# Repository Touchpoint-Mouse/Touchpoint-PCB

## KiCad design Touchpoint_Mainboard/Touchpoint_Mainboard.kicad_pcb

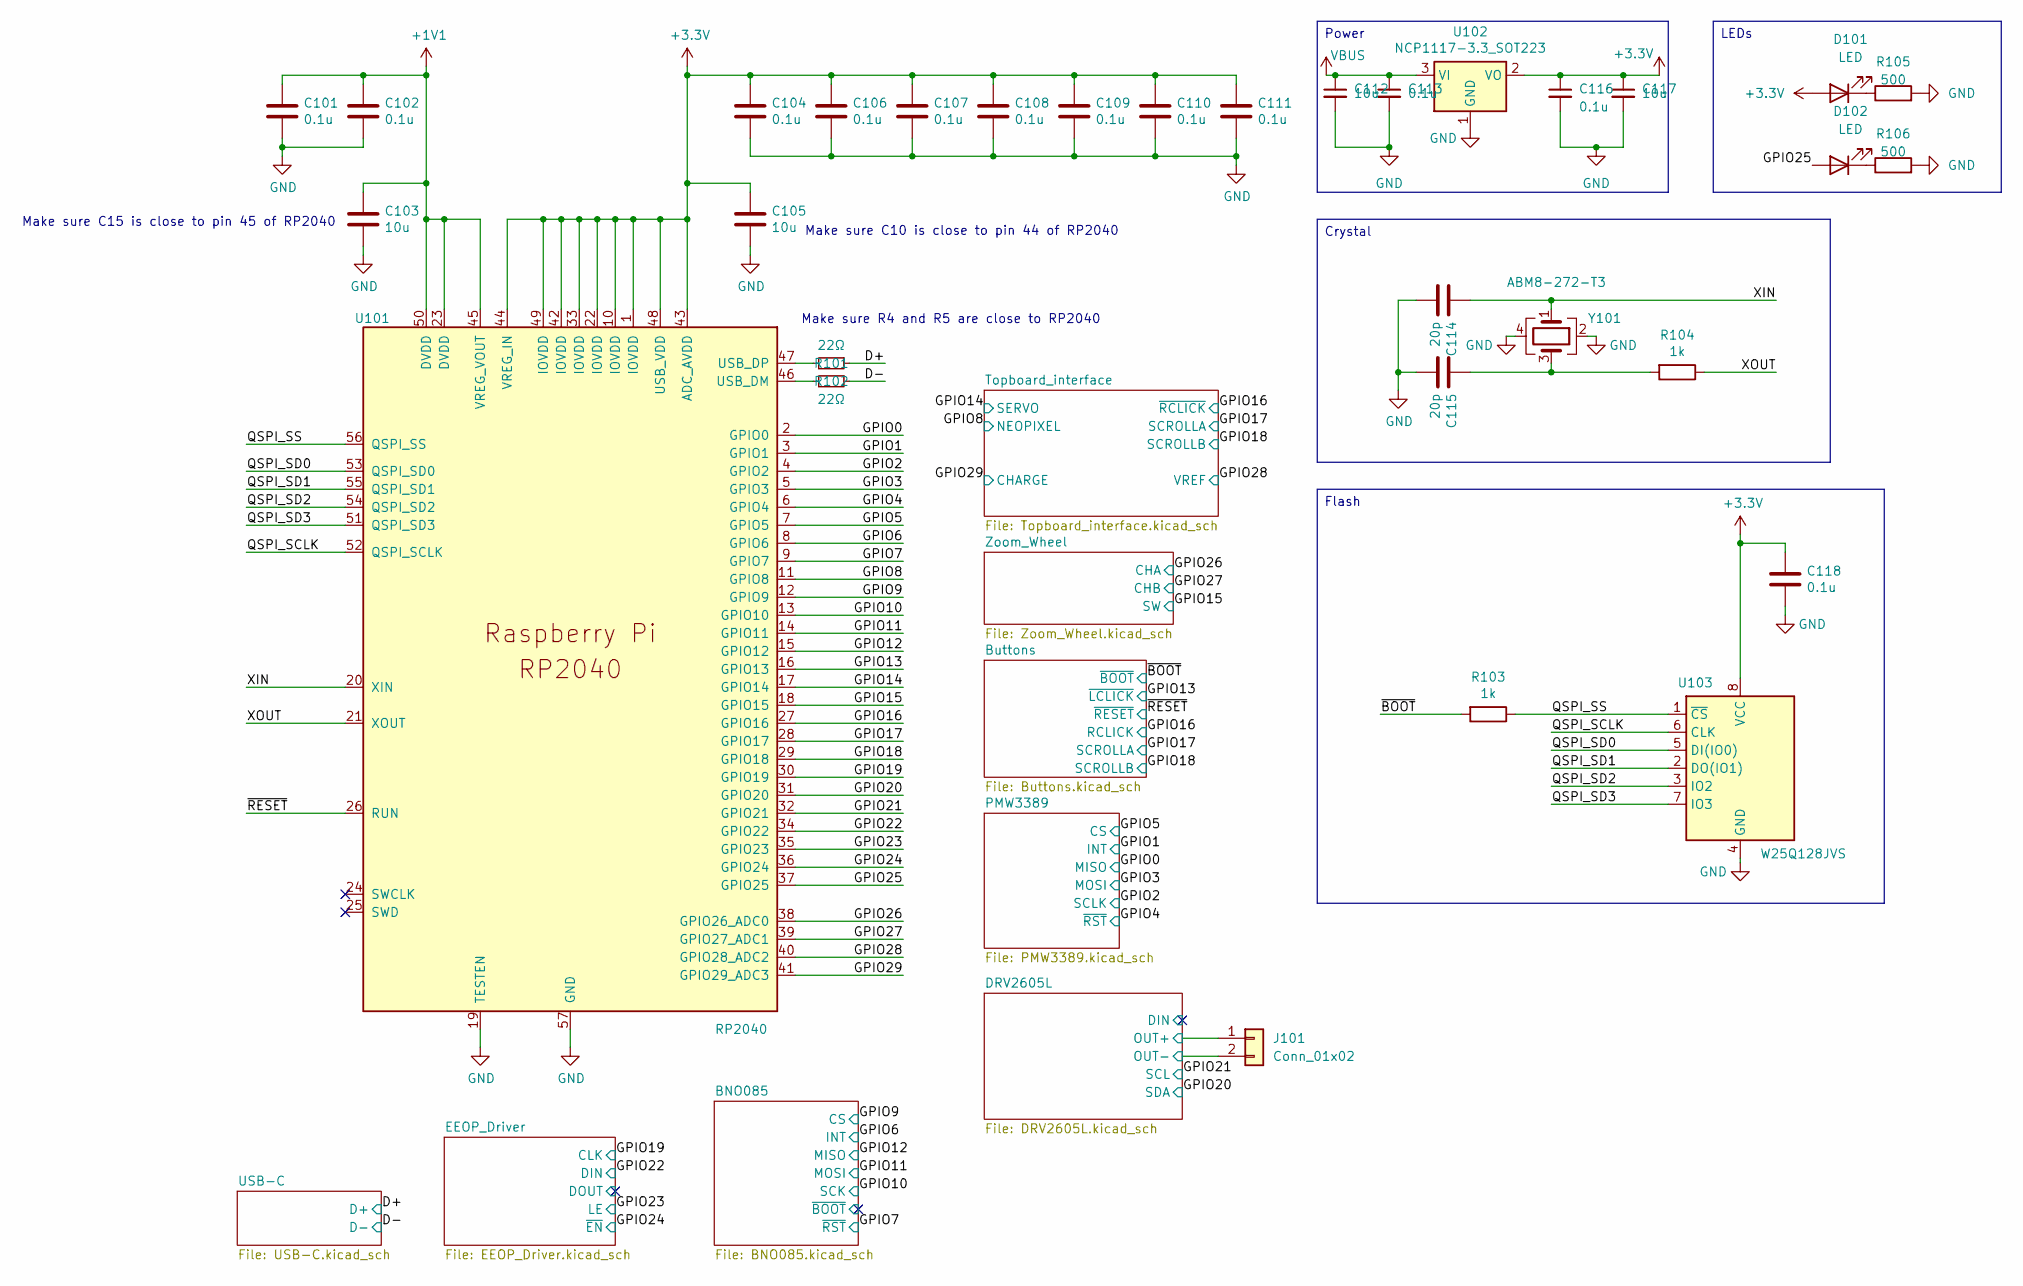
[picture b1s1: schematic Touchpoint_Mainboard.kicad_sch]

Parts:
C101, C102, C104, C106, C107, C108, C109, C110, C111, C113, C116, C118: 0.1u; C_0402_1005Metric
C103, C105, C112, C117: 10u; C_0805_2012Metric
C114, C115: 20p; C_0402_1005Metric
D101, D102: LED; LED_0603_1608Metric
J101: Conn_01x02; SolderWire-0.1sqmm_1x02_P3.6mm_D0.4mm_OD1mm
R101, R102: 22Ω; R_0402_1005Metric; LCSC C23345
R103, R104: 1k; R_0402_1005Metric
R105, R106: 500; R_0402_1005Metric
U101: RP2040; QFN-56-1EP_7x7mm_P0.4mm_EP3.2x3.2mm
U102: NCP1117-3.3_SOT223; SOT-223-3_TabPin2
U103: W25Q128JVS; SOIC-8_5.3x5.3mm_P1.27mm
Y101: ABM8-272-T3; Crystal_SMD_3225-4Pin_3.2x2.5mm

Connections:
+1V1: C101.1, C102.1, C103.1, U101.23 (DVDD), U101.45 (VREG_VOUT), U101.50 (DVDD)
+3.3V: C104.1, C105.1, C106.1, C107.1, C108.1, C109.1, C110.1, C111.1, C116.1, C117.1, C118.1, D101.2 (A), U101.1 (IOVDD), U101.10 (IOVDD), U101.22 (IOVDD), U101.33 (IOVDD), U101.42 (IOVDD), U101.43 (ADC_AVDD), U101.44 (VREG_IN), U101.48 (USB_VDD), U101.49 (IOVDD), U102.2 (VO), U103.8 (VCC); also elsewhere on the board
/D+: R101.1; also elsewhere on the board
/D-: R102.1; also elsewhere on the board
/DRV2605L/OUT+: J101.1; also elsewhere on the board
/DRV2605L/OUT-: J101.2; also elsewhere on the board
/GPIO0: U101.2 (GPIO0); also elsewhere on the board
/GPIO1: U101.3 (GPIO1); also elsewhere on the board
/GPIO2: U101.4 (GPIO2); also elsewhere on the board
/GPIO3: U101.5 (GPIO3); also elsewhere on the board
/GPIO4: U101.6 (GPIO4); also elsewhere on the board
/GPIO5: U101.7 (GPIO5); also elsewhere on the board
/GPIO6: U101.8 (GPIO6); also elsewhere on the board
/GPIO7: U101.9 (GPIO7); also elsewhere on the board
/GPIO8: U101.11 (GPIO8); also elsewhere on the board
/GPIO9: U101.12 (GPIO9); also elsewhere on the board
/GPIO10: U101.13 (GPIO10); also elsewhere on the board
/GPIO11: U101.14 (GPIO11); also elsewhere on the board
/GPIO12: U101.15 (GPIO12); also elsewhere on the board
/GPIO13: U101.16 (GPIO13); also elsewhere on the board
/GPIO14: U101.17 (GPIO14); also elsewhere on the board
/GPIO15: U101.18 (GPIO15); also elsewhere on the board
/GPIO16: U101.27 (GPIO16); also elsewhere on the board
/GPIO17: U101.28 (GPIO17); also elsewhere on the board
/GPIO18: U101.29 (GPIO18); also elsewhere on the board
/GPIO19: U101.30 (GPIO19); also elsewhere on the board
/GPIO20: U101.31 (GPIO20); also elsewhere on the board
/GPIO21: U101.32 (GPIO21); also elsewhere on the board
/GPIO22: U101.34 (GPIO22); also elsewhere on the board
/GPIO23: U101.35 (GPIO23); also elsewhere on the board
/GPIO24: U101.36 (GPIO24); also elsewhere on the board
/GPIO25: D102.2 (A), U101.37 (GPIO25)
/GPIO26: U101.38 (GPIO26_ADC0); also elsewhere on the board
/GPIO27: U101.39 (GPIO27_ADC1); also elsewhere on the board
/GPIO28: U101.40 (GPIO28_ADC2); also elsewhere on the board
/GPIO29: U101.41 (GPIO29_ADC3); also elsewhere on the board
/QSPI_SCLK: U101.52 (QSPI_SCLK), U103.6 (CLK)
/QSPI_SD0: U101.53 (QSPI_SD0), U103.5 (DI(IO0))
/QSPI_SD1: U101.55 (QSPI_SD1), U103.2 (DO(IO1))
/QSPI_SD2: U101.54 (QSPI_SD2), U103.3 (IO2)
/QSPI_SD3: U101.51 (QSPI_SD3), U103.7 (IO3)
/QSPI_SS: R103.1, U101.56 (QSPI_SS), U103.1 (~CS)
/XIN: C114.1, U101.20 (XIN), Y101.1
/XOUT: R104.1, U101.21 (XOUT)
/~BOOT: R103.2; also elsewhere on the board
/~RESET: U101.26 (RUN); also elsewhere on the board
GND: C101.2, C102.2, C103.2, C104.2, C105.2, C106.2, C107.2, C108.2, C109.2, C110.2, C111.2, C112.2, C113.2, C114.2, C115.2, C116.2, C117.2, C118.2, R105.2, R106.2, U101.19 (TESTEN), U101.57 (GND), U102.1 (GND), U103.4 (GND), Y101.2, Y101.4; also elsewhere on the board
unnamed: C115.1, R104.2, Y101.3
unnamed: D101.1 (K), R105.1
unnamed: D102.1 (K), R106.1
unnamed: R102.2, U101.46 (USB_DM)
unnamed: R101.2, U101.47 (USB_DP)
VBUS: C112.1, C113.1, U102.3 (VI); also elsewhere on the board

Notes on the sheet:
Make sure R4 and R5 are close to RP2040
Make sure C10 is close to pin 44 of RP2040
Make sure C15 is close to pin 45 of RP2040
Flash
LEDs
Crystal
Power

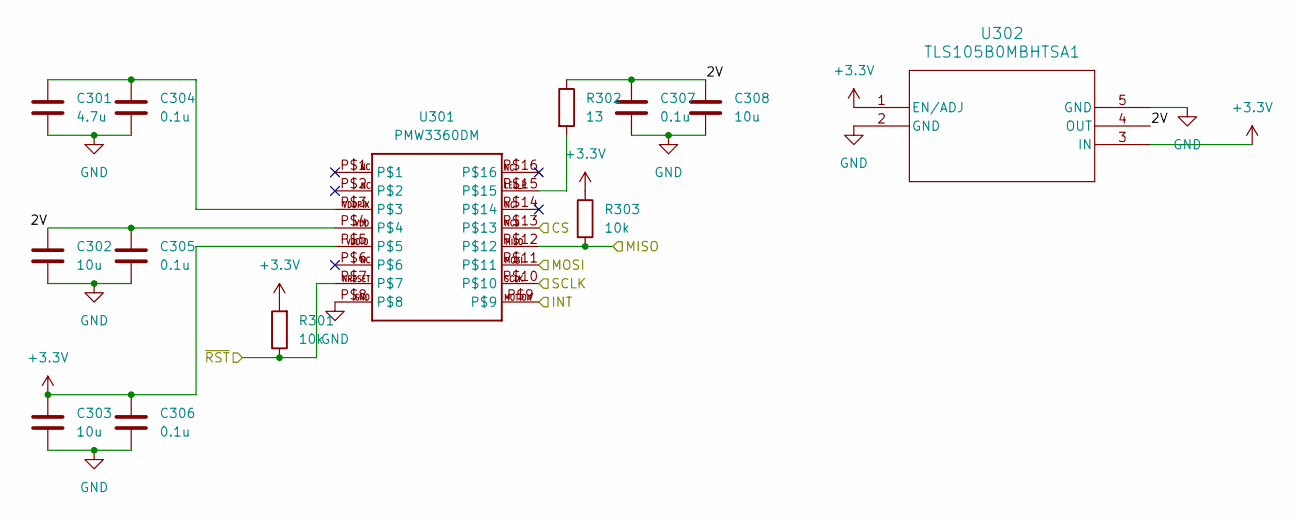
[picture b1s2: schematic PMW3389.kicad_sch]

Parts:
C301: 4.7u; C_0402_1005Metric
C302, C303, C308: 10u; C_0805_2012Metric
C304, C305, C306, C307: 0.1u; C_0402_1005Metric
R301, R303: 10k; R_0402_1005Metric
R302: 13; R_0402_1005Metric
U301: PMW3360DM
U302: TLS105B0MBHTSA1; PG-SCT-595-5_INF

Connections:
+3.3V: C303.1, C306.1, R301.2, R303.1, U301.P$5, U302.1 (EN/ADJ), U302.3 (IN); also elsewhere on the board
/GPIO0: R303.2, U301.P$12; also elsewhere on the board
/GPIO1: U301.P$9; also elsewhere on the board
/GPIO2: U301.P$10; also elsewhere on the board
/GPIO3: U301.P$11; also elsewhere on the board
/GPIO4: R301.1, U301.P$7; also elsewhere on the board
/GPIO5: U301.P$13; also elsewhere on the board
/PMW3389/2V: C302.1, C305.1, C307.1, C308.1, R302.1, U301.P$4, U302.4 (OUT)
GND: C301.2, C302.2, C303.2, C304.2, C305.2, C306.2, C307.2, C308.2, U301.P$8, U302.2 (GND), U302.5 (GND); also elsewhere on the board
unnamed: C301.1, C304.1, U301.P$3
unnamed: R302.2, U301.P$15

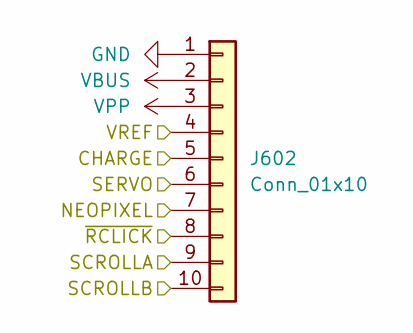
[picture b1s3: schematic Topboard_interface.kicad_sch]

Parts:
J602: Conn_01x10; Jumper_Interface_10

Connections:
/GPIO8: J602.7; also elsewhere on the board
/GPIO14: J602.6; also elsewhere on the board
/GPIO16: J602.8; also elsewhere on the board
/GPIO17: J602.9; also elsewhere on the board
/GPIO18: J602.10; also elsewhere on the board
/GPIO28: J602.4; also elsewhere on the board
/GPIO29: J602.5; also elsewhere on the board
GND: J602.1; also elsewhere on the board
VBUS: J602.2; also elsewhere on the board
VPP: J602.3; also elsewhere on the board

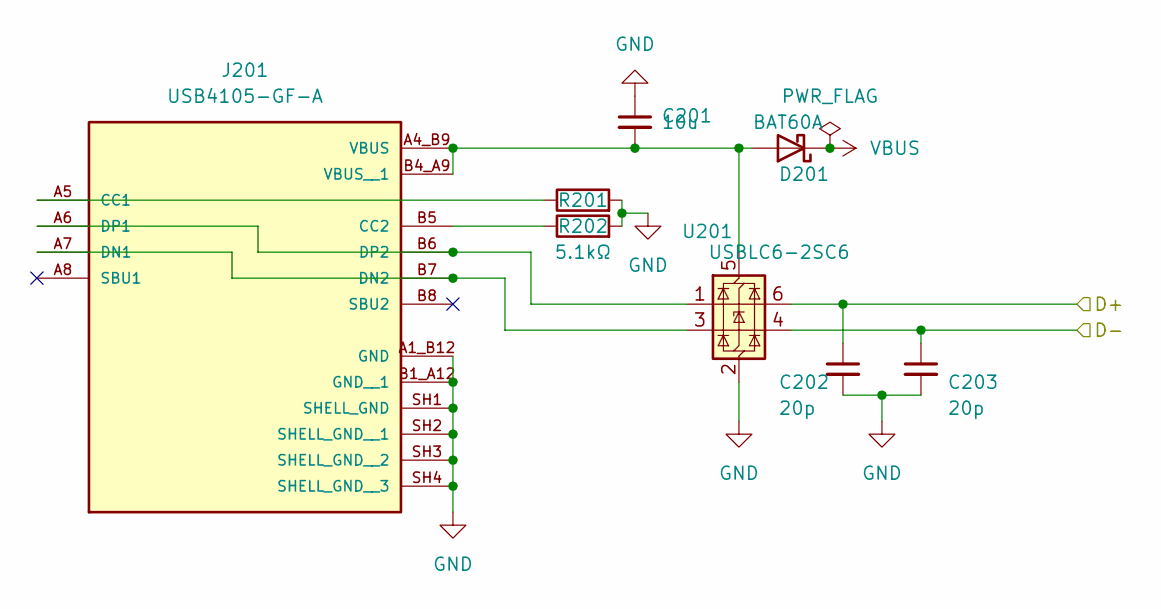
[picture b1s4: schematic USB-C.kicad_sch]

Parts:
C201: 10u; C_0805_2012Metric
C202, C203: 20p; C_0402_1005Metric; LCSC C1648
D201: BAT60A; D_SOD-323; JLCPCB C124187
J201: USB4105-GF-A; GCT_USB4105-GF-A; PARTREV B4
R201, R202: 5.1kΩ; R_0402_1005Metric; JLCPCB C23186
U201: USBLC6-2SC6; SOT-23-6; JLCPCB C2827654

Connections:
/D+: C202.1, U201.6 (I/O1); also elsewhere on the board
/D-: C203.1, U201.4 (I/O2); also elsewhere on the board
GND: C201.1, C202.2, C203.2, J201.A1_B12 (GND), J201.B1_A12 (GND__1), J201.SH1 (SHELL_GND), J201.SH2 (SHELL_GND__1), J201.SH3 (SHELL_GND__2), J201.SH4 (SHELL_GND__3), R201.2, R202.2, U201.2 (GND); also elsewhere on the board
unnamed: C201.2, D201.2 (A), J201.A4_B9 (VBUS), J201.B4_A9 (VBUS__1), U201.5 (VBUS)
unnamed: J201.A5 (CC1), R201.1
unnamed: J201.B5 (CC2), R202.1
unnamed: J201.A7 (DN1), J201.B7 (DN2), U201.3 (I/O2)
unnamed: J201.A6 (DP1), J201.B6 (DP2), U201.1 (I/O1)
VBUS: D201.1 (K); also elsewhere on the board

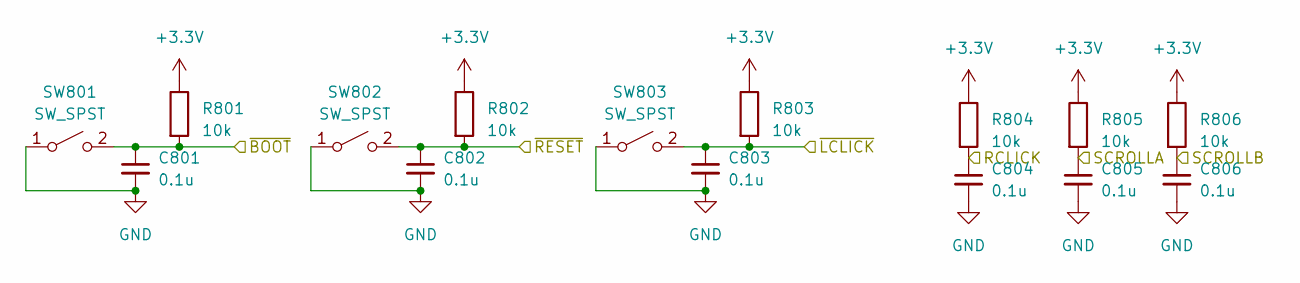
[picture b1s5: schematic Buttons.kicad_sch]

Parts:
C801, C802, C803, C804, C805, C806: 0.1u; C_0402_1005Metric
R801, R802, R803, R804, R805, R806: 10k; R_0402_1005Metric
SW801, SW802: SW_SPST; SW_PUSH_6mm
SW803: SW_SPST; SolderWire-0.1sqmm_1x02_P3.6mm_D0.4mm_OD1mm

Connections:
+3.3V: R801.1, R802.1, R803.1, R804.1, R805.1, R806.1; also elsewhere on the board
/GPIO13: C803.1, R803.2, SW803.2 (B); also elsewhere on the board
/GPIO16: C804.1, R804.2; also elsewhere on the board
/GPIO17: C805.1, R805.2; also elsewhere on the board
/GPIO18: C806.1, R806.2; also elsewhere on the board
/~BOOT: C801.1, R801.2, SW801.2 (B); also elsewhere on the board
/~RESET: C802.1, R802.2, SW802.2 (B); also elsewhere on the board
GND: C801.2, C802.2, C803.2, C804.2, C805.2, C806.2, SW801.1 (A), SW802.1 (A), SW803.1 (A); also elsewhere on the board

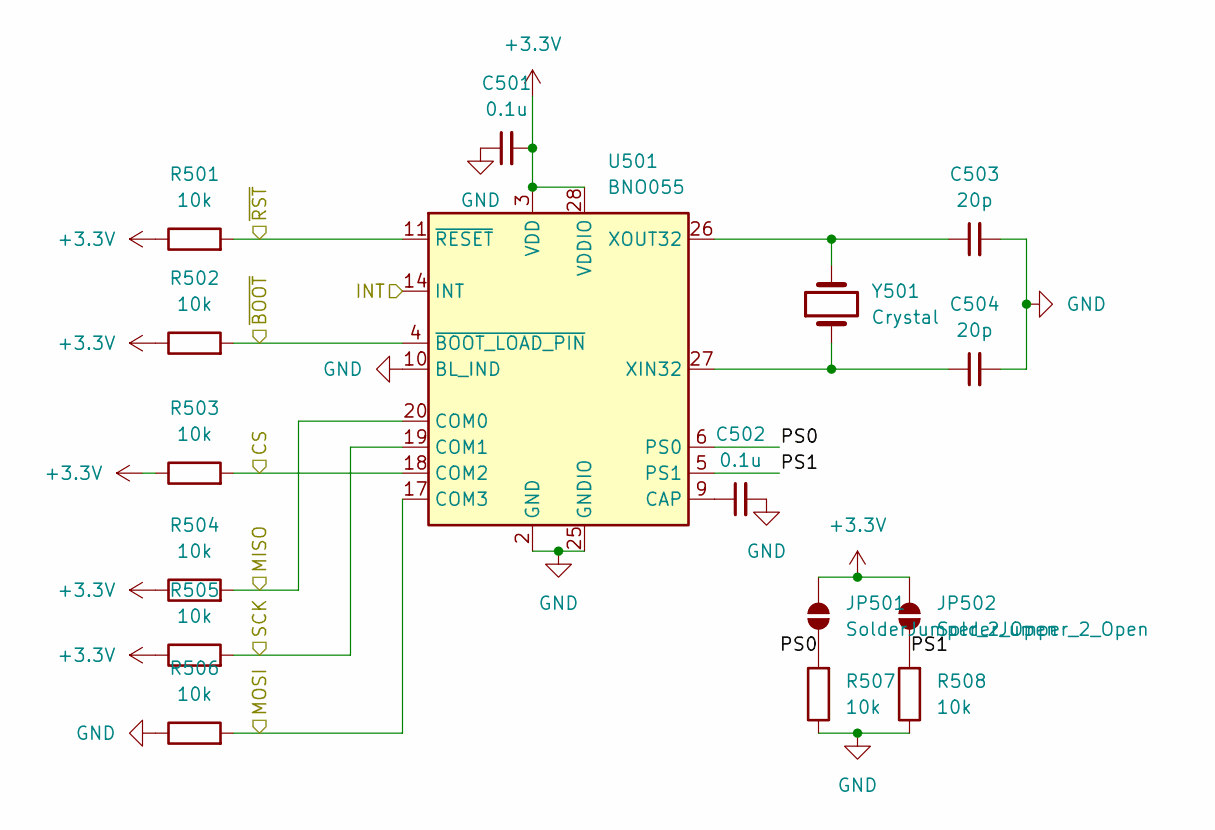
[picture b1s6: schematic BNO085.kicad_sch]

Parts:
C501, C502: 0.1u; C_0402_1005Metric
C503, C504: 20p; C_0402_1005Metric
JP501, JP502: SolderJumper_2_Open; SolderJumper-2_P1.3mm_Open_RoundedPad1.0x1.5mm
R501, R502, R503, R504, R505, R506, R507, R508: 10k; R_0402_1005Metric
U501: BNO055; LGA-28_5.2x3.8mm_P0.5mm
Y501: Crystal; XTAL_MU00525_NDK

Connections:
+3.3V: C501.2, JP501.2 (B), JP502.2 (B), R501.1, R502.1, R503.1, R504.1, R505.1, U501.3 (VDD), U501.28 (VDDIO); also elsewhere on the board
/BNO085/PS0: JP501.1 (A), R507.2, U501.6 (PS0)
/BNO085/PS1: JP502.1 (A), R508.2, U501.5 (PS1)
/BNO085/~BOOT: R502.2, U501.4 (~BOOT_LOAD_PIN)
/GPIO6: U501.14 (INT); also elsewhere on the board
/GPIO7: R501.2, U501.11 (~RESET); also elsewhere on the board
/GPIO9: R503.2, U501.18 (COM2); also elsewhere on the board
/GPIO10: R505.2, U501.19 (COM1); also elsewhere on the board
/GPIO11: R506.2, U501.17 (COM3); also elsewhere on the board
/GPIO12: R504.2, U501.20 (COM0); also elsewhere on the board
GND: C501.1, C502.2, C503.2, C504.2, R506.1, R507.1, R508.1, U501.2 (GND), U501.10 (BL_IND), U501.25 (GNDIO); also elsewhere on the board
unnamed: C502.1, U501.9 (CAP)
unnamed: C504.1, U501.27 (XIN32), Y501.1
unnamed: C503.1, U501.26 (XOUT32), Y501.2

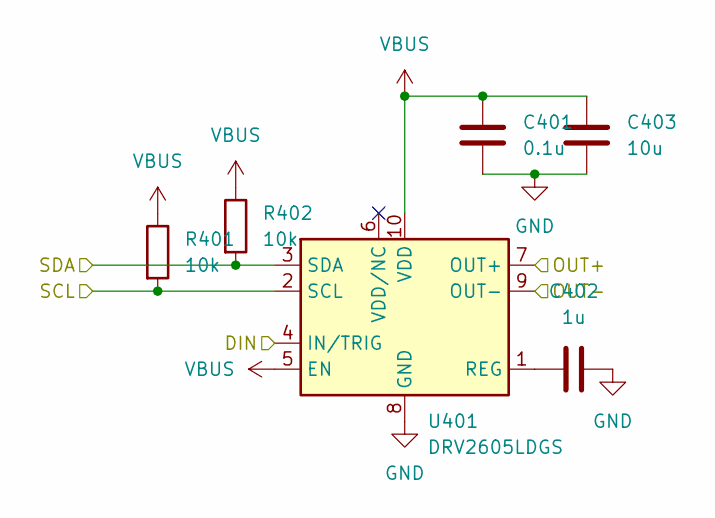
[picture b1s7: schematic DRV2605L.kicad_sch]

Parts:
C401: 0.1u; C_0402_1005Metric
C402: 1u; C_0402_1005Metric
C403: 10u; C_0805_2012Metric
R401, R402: 10k; R_0402_1005Metric
U401: DRV2605LDGS; VSSOP-10_3x3mm_P0.5mm

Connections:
/DRV2605L/DIN: U401.4 (IN/TRIG)
/DRV2605L/OUT+: U401.7 (OUT+); also elsewhere on the board
/DRV2605L/OUT-: U401.9 (OUT-); also elsewhere on the board
/GPIO20: R402.2, U401.3 (SDA); also elsewhere on the board
/GPIO21: R401.2, U401.2 (SCL); also elsewhere on the board
GND: C401.2, C402.2, C403.2, U401.8 (GND); also elsewhere on the board
unnamed: C402.1, U401.1 (REG)
VBUS: C401.1, C403.1, R401.1, R402.1, U401.5 (EN), U401.10 (VDD); also elsewhere on the board

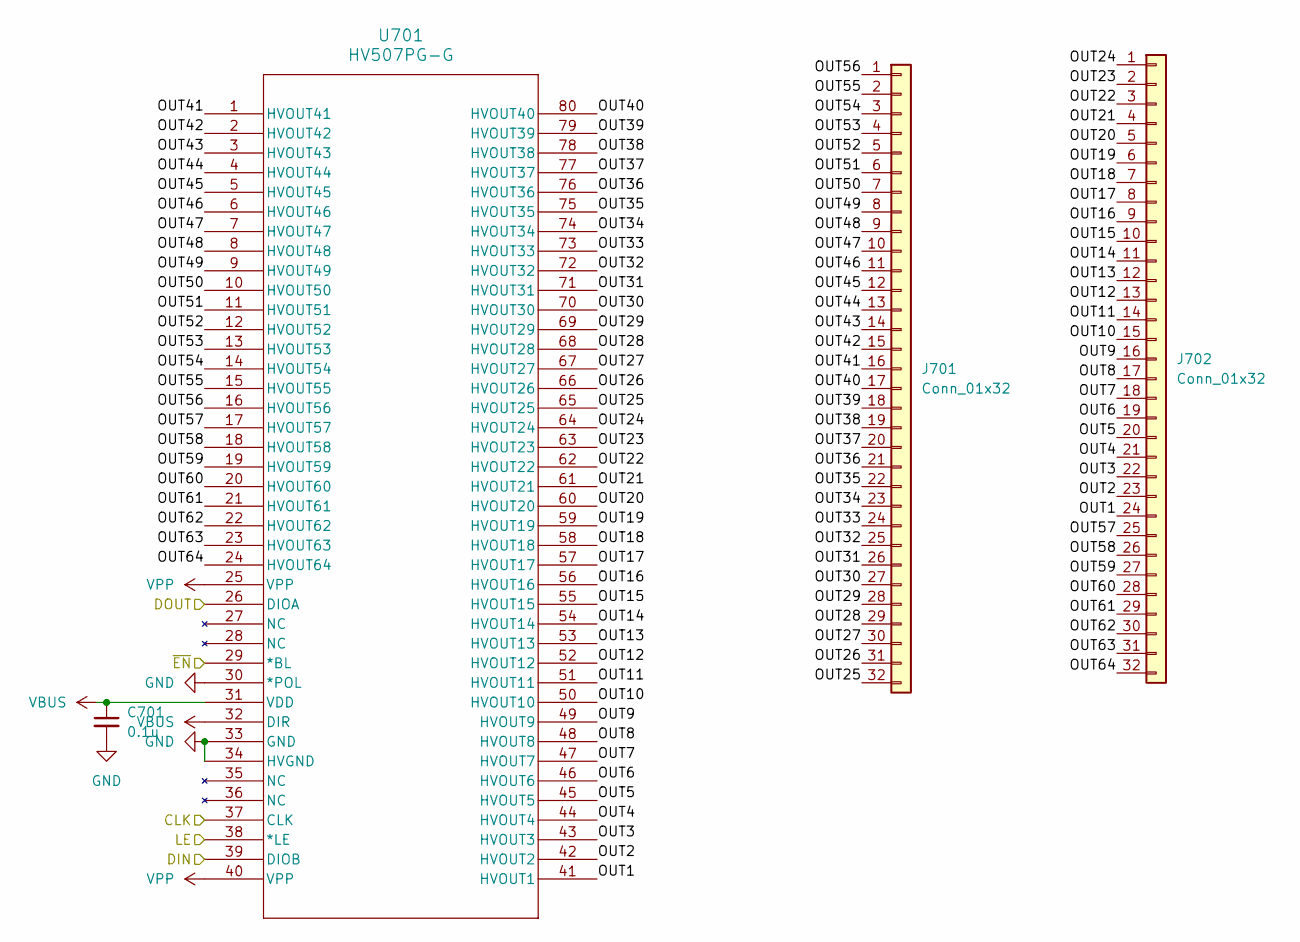
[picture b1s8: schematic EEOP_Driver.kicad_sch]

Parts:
C701: 0.1u; C_0402_1005Metric
J701, J702: Conn_01x32; HRS_FH34SRJ-32S-0.5SH_50_
U701: HV507PG-G; PQFP-80_14x20mm_P0.8mm

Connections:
/EEOP_Driver/DOUT: U701.26 (DIOA)
/EEOP_Driver/OUT1: J702.24, U701.41 (HVOUT1)
/EEOP_Driver/OUT2: J702.23, U701.42 (HVOUT2)
/EEOP_Driver/OUT3: J702.22, U701.43 (HVOUT3)
/EEOP_Driver/OUT4: J702.21, U701.44 (HVOUT4)
/EEOP_Driver/OUT5: J702.20, U701.45 (HVOUT5)
/EEOP_Driver/OUT6: J702.19, U701.46 (HVOUT6)
/EEOP_Driver/OUT7: J702.18, U701.47 (HVOUT7)
/EEOP_Driver/OUT8: J702.17, U701.48 (HVOUT8)
/EEOP_Driver/OUT9: J702.16, U701.49 (HVOUT9)
/EEOP_Driver/OUT10: J702.15, U701.50 (HVOUT10)
/EEOP_Driver/OUT11: J702.14, U701.51 (HVOUT11)
/EEOP_Driver/OUT12: J702.13, U701.52 (HVOUT12)
/EEOP_Driver/OUT13: J702.12, U701.53 (HVOUT13)
/EEOP_Driver/OUT14: J702.11, U701.54 (HVOUT14)
/EEOP_Driver/OUT15: J702.10, U701.55 (HVOUT15)
/EEOP_Driver/OUT16: J702.9, U701.56 (HVOUT16)
/EEOP_Driver/OUT17: J702.8, U701.57 (HVOUT17)
/EEOP_Driver/OUT18: J702.7, U701.58 (HVOUT18)
/EEOP_Driver/OUT19: J702.6, U701.59 (HVOUT19)
/EEOP_Driver/OUT20: J702.5, U701.60 (HVOUT20)
/EEOP_Driver/OUT21: J702.4, U701.61 (HVOUT21)
/EEOP_Driver/OUT22: J702.3, U701.62 (HVOUT22)
/EEOP_Driver/OUT23: J702.2, U701.63 (HVOUT23)
/EEOP_Driver/OUT24: J702.1, U701.64 (HVOUT24)
/EEOP_Driver/OUT25: J701.32, U701.65 (HVOUT25)
/EEOP_Driver/OUT26: J701.31, U701.66 (HVOUT26)
/EEOP_Driver/OUT27: J701.30, U701.67 (HVOUT27)
/EEOP_Driver/OUT28: J701.29, U701.68 (HVOUT28)
/EEOP_Driver/OUT29: J701.28, U701.69 (HVOUT29)
/EEOP_Driver/OUT30: J701.27, U701.70 (HVOUT30)
/EEOP_Driver/OUT31: J701.26, U701.71 (HVOUT31)
/EEOP_Driver/OUT32: J701.25, U701.72 (HVOUT32)
/EEOP_Driver/OUT33: J701.24, U701.73 (HVOUT33)
/EEOP_Driver/OUT34: J701.23, U701.74 (HVOUT34)
/EEOP_Driver/OUT35: J701.22, U701.75 (HVOUT35)
/EEOP_Driver/OUT36: J701.21, U701.76 (HVOUT36)
/EEOP_Driver/OUT37: J701.20, U701.77 (HVOUT37)
/EEOP_Driver/OUT38: J701.19, U701.78 (HVOUT38)
/EEOP_Driver/OUT39: J701.18, U701.79 (HVOUT39)
/EEOP_Driver/OUT40: J701.17, U701.80 (HVOUT40)
/EEOP_Driver/OUT41: J701.16, U701.1 (HVOUT41)
/EEOP_Driver/OUT42: J701.15, U701.2 (HVOUT42)
/EEOP_Driver/OUT43: J701.14, U701.3 (HVOUT43)
/EEOP_Driver/OUT44: J701.13, U701.4 (HVOUT44)
/EEOP_Driver/OUT45: J701.12, U701.5 (HVOUT45)
/EEOP_Driver/OUT46: J701.11, U701.6 (HVOUT46)
/EEOP_Driver/OUT47: J701.10, U701.7 (HVOUT47)
/EEOP_Driver/OUT48: J701.9, U701.8 (HVOUT48)
/EEOP_Driver/OUT49: J701.8, U701.9 (HVOUT49)
/EEOP_Driver/OUT50: J701.7, U701.10 (HVOUT50)
/EEOP_Driver/OUT51: J701.6, U701.11 (HVOUT51)
/EEOP_Driver/OUT52: J701.5, U701.12 (HVOUT52)
/EEOP_Driver/OUT53: J701.4, U701.13 (HVOUT53)
/EEOP_Driver/OUT54: J701.3, U701.14 (HVOUT54)
/EEOP_Driver/OUT55: J701.2, U701.15 (HVOUT55)
/EEOP_Driver/OUT56: J701.1, U701.16 (HVOUT56)
/EEOP_Driver/OUT57: J702.25, U701.17 (HVOUT57)
/EEOP_Driver/OUT58: J702.26, U701.18 (HVOUT58)
/EEOP_Driver/OUT59: J702.27, U701.19 (HVOUT59)
/EEOP_Driver/OUT60: J702.28, U701.20 (HVOUT60)
/EEOP_Driver/OUT61: J702.29, U701.21 (HVOUT61)
/EEOP_Driver/OUT62: J702.30, U701.22 (HVOUT62)
/EEOP_Driver/OUT63: J702.31, U701.23 (HVOUT63)
/EEOP_Driver/OUT64: J702.32, U701.24 (HVOUT64)
/GPIO19: U701.37 (CLK); also elsewhere on the board
/GPIO22: U701.39 (DIOB); also elsewhere on the board
/GPIO23: U701.38 (*LE); also elsewhere on the board
/GPIO24: U701.29 (*BL); also elsewhere on the board
GND: C701.2, U701.30 (*POL), U701.33 (GND), U701.34 (HVGND); also elsewhere on the board
VBUS: C701.1, U701.31 (VDD), U701.32 (DIR); also elsewhere on the board
VPP: U701.25 (VPP), U701.40 (VPP); also elsewhere on the board

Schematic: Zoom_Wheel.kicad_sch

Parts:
C901, C902, C903: 0.1u; C_0402_1005Metric
R901, R902, R903: 10k; R_0402_1005Metric
S901: PEC12R-4220F-S0024; XDCR_PEC12R-4220F-S0024; PARTREV 07/21; DigiKey_Part_Number PEC12R-4220F-S0024-ND

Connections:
+3.3V: R901.1, R902.1, R903.1; also elsewhere on the board
/GPIO15: C903.2, R903.2, S901.2; also elsewhere on the board
/GPIO26: C901.2, R901.2, S901.A (CHANNEL_A); also elsewhere on the board
/GPIO27: C902.2, R902.2, S901.B (CHANNEL_B); also elsewhere on the board
GND: C901.1, C902.1, C903.1, S901.1, S901.C (COMMON); also elsewhere on the board

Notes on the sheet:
Zoom Wheel

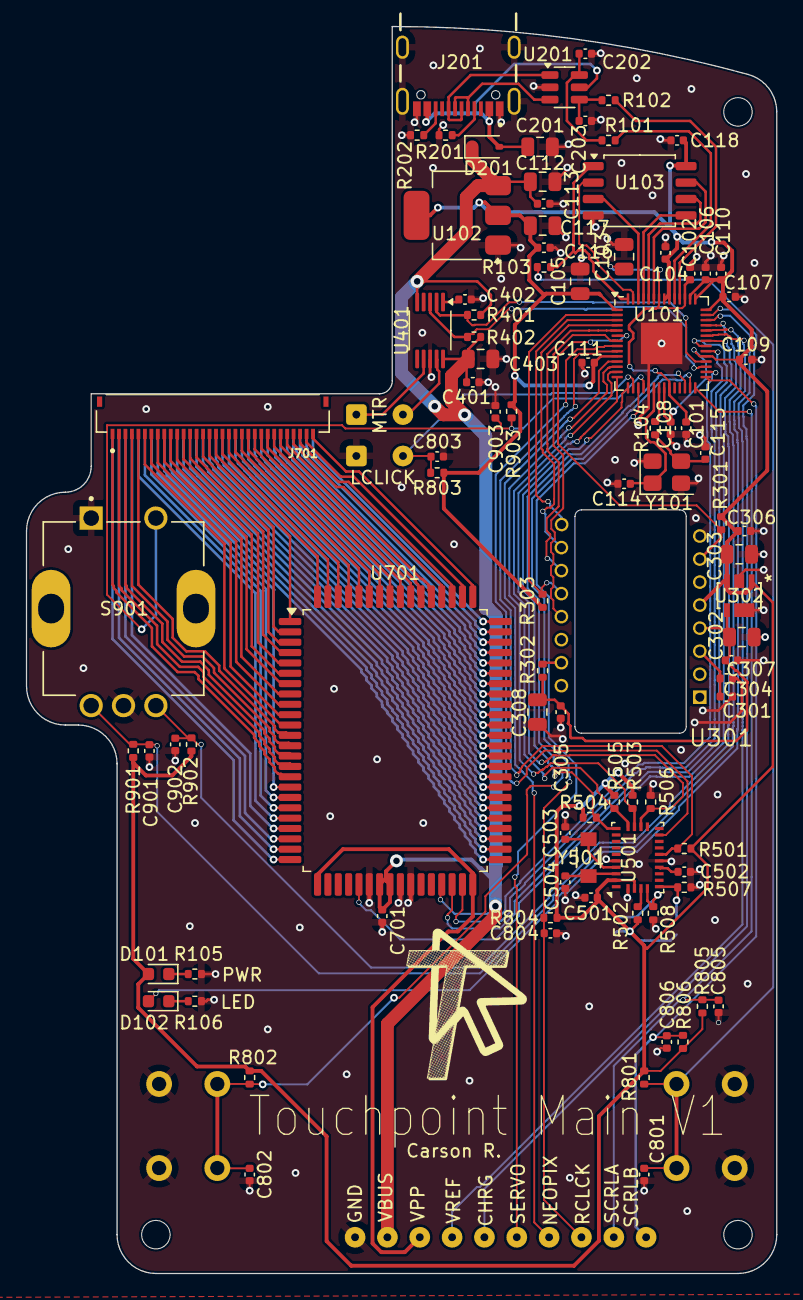
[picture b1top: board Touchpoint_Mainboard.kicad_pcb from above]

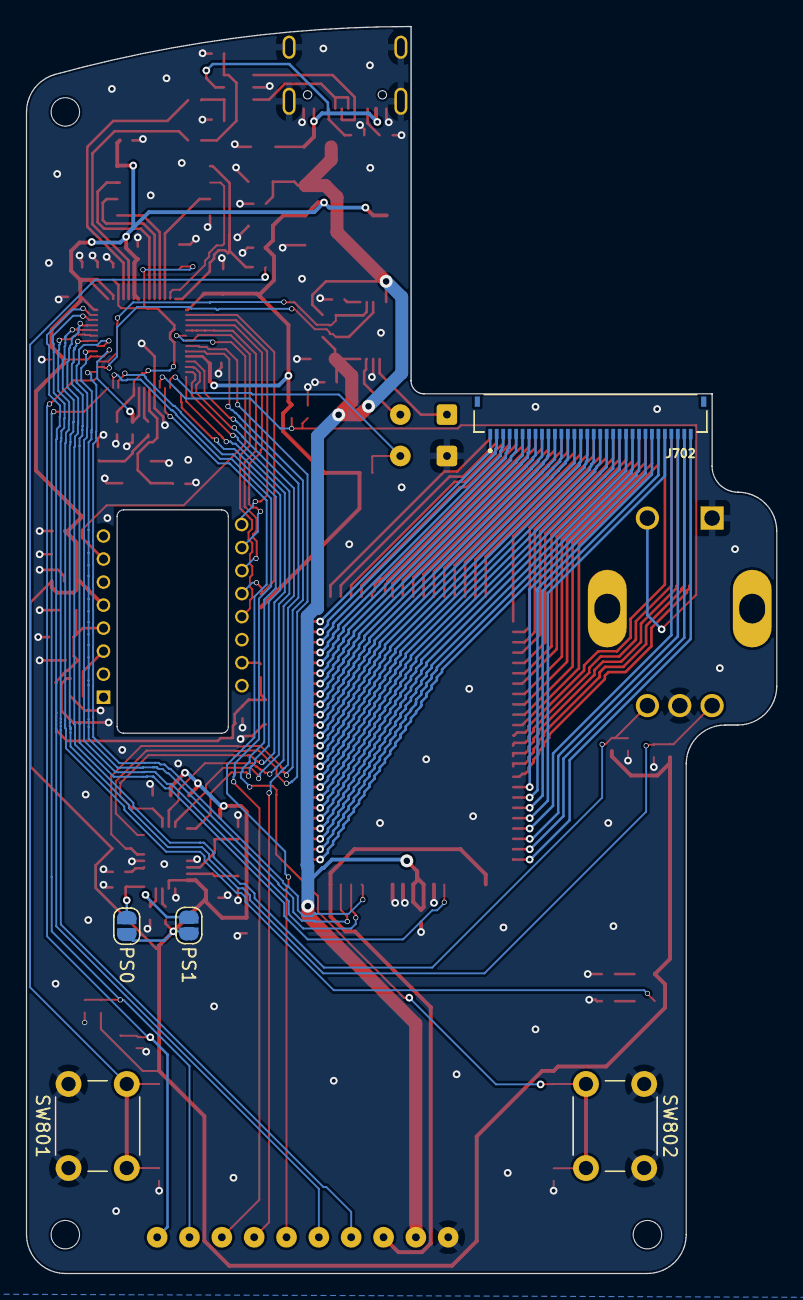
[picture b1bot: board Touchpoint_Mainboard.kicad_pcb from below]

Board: 2 copper layers, 58.0 x 96.4 mm, 101 parts (5 on the bottom side), 133 nets.

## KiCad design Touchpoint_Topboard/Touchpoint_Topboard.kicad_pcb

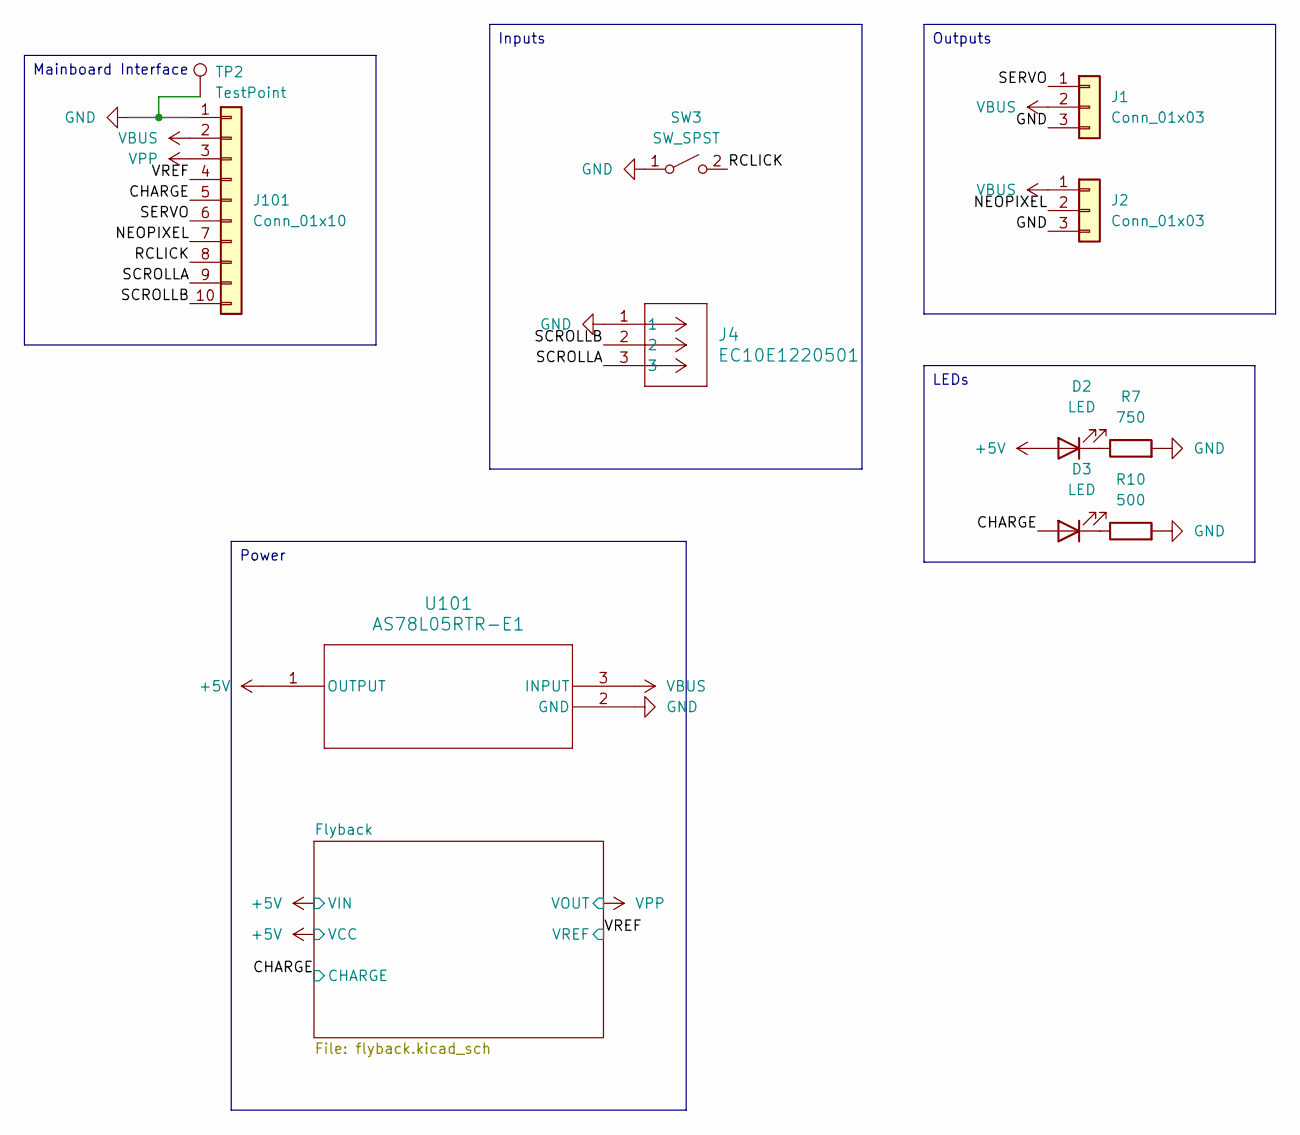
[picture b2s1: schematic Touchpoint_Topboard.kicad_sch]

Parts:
D2, D3: LED; LED_0603_1608Metric
J1, J2: Conn_01x03; PinHeader_1x03_P2.54mm_Vertical
J4: EC10E1220501; CONN03_EC10E_9P8X6P1_ALPS
J101: Conn_01x10; Jumper_Interface_10
R7: 750; R_0402_1005Metric
R10: 500; R_0402_1005Metric
SW3: SW_SPST; SW_SPST_EVQP0
TP2: TestPoint; TestPoint_Keystone_5019_Miniature
U101: AS78L05RTR-E1; SOT-89_3MC_MCH

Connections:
+5V: D2.2 (A), U101.1 (OUTPUT); also elsewhere on the board
/CHARGE: D3.2 (A), J101.5; also elsewhere on the board
/NEOPIXEL: J2.2, J101.7
/RCLICK: J101.8, SW3.2 (B)
/SCROLLA: J4.3, J101.9
/SCROLLB: J4.2, J101.10
/SERVO: J1.1, J101.6
/VREF: J101.4; also elsewhere on the board
GND: J1.3, J2.3, J4.1, J101.1, R7.2, R10.2, SW3.1 (A), TP2.1, U101.2 (GND); also elsewhere on the board
unnamed: D2.1 (K), R7.1
unnamed: D3.1 (K), R10.1
VBUS: J1.2, J2.1, J101.2, U101.3 (INPUT)
VPP: J101.3; also elsewhere on the board

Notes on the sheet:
Mainboard Interface
Outputs
Inputs
LEDs
Power

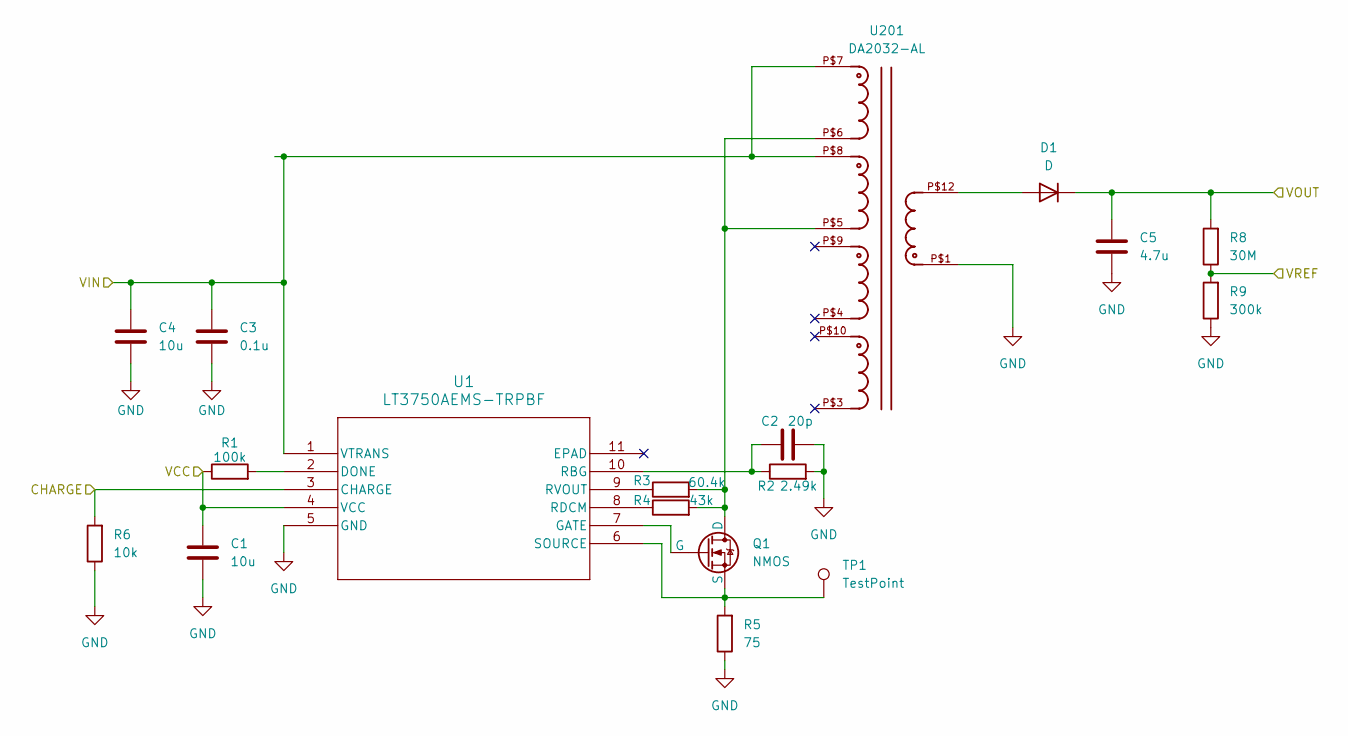
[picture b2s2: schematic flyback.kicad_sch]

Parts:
C1, C4: 10u; C_0805_2012Metric
C2: 20p; C_0402_1005Metric
C3: 0.1u; C_0402_1005Metric
C5: 4.7u; CP_Radial_D8.0mm_P3.50mm
D1: D; SMB_DIO
Q1: NMOS; SOT-89_3MC_MCH
R1: 100k; R_0402_1005Metric
R2: 2.49k; R_0402_1005Metric
R3: 60.4k; R_0402_1005Metric
R4: 43k; R_0402_1005Metric
R5: 75; R_0402_1005Metric
R6: 10k; R_0402_1005Metric
R8: 30M; R_0402_1005Metric
R9: 300k; R_0402_1005Metric
TP1: TestPoint; TestPoint_Keystone_5019_Miniature
U1: LT3750AEMS-TRPBF; MSOP-10-1EP_3x3mm_P0.5mm_EP1.68x1.88mm
U201: DA2032-AL

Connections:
+5V: C1.1, C3.1, C4.1, R1.1, U1.1 (VTRANS), U1.4 (VCC), U201.P$7, U201.P$8; also elsewhere on the board
/CHARGE: R6.2, U1.3 (CHARGE); also elsewhere on the board
/VREF: R8.1, R9.2; also elsewhere on the board
GND: C1.2, C2.1, C3.2, C4.2, C5.2, R2.2, R5.1, R6.1, R9.1, U1.5 (GND), U201.P$1; also elsewhere on the board
unnamed: D1.2 (A), U201.P$12
unnamed: Q1.1 (D), R3.2, R4.2, U201.P$5, U201.P$6
unnamed: Q1.2 (G), U1.7 (GATE)
unnamed: Q1.3 (S), R5.2, TP1.1, U1.6 (SOURCE)
unnamed: R1.2, U1.2 (DONE)
unnamed: C2.2, R2.1, U1.10 (RBG)
unnamed: R4.1, U1.8 (RDCM)
unnamed: R3.1, U1.9 (RVOUT)
VPP: C5.1, D1.1 (K), R8.2; also elsewhere on the board

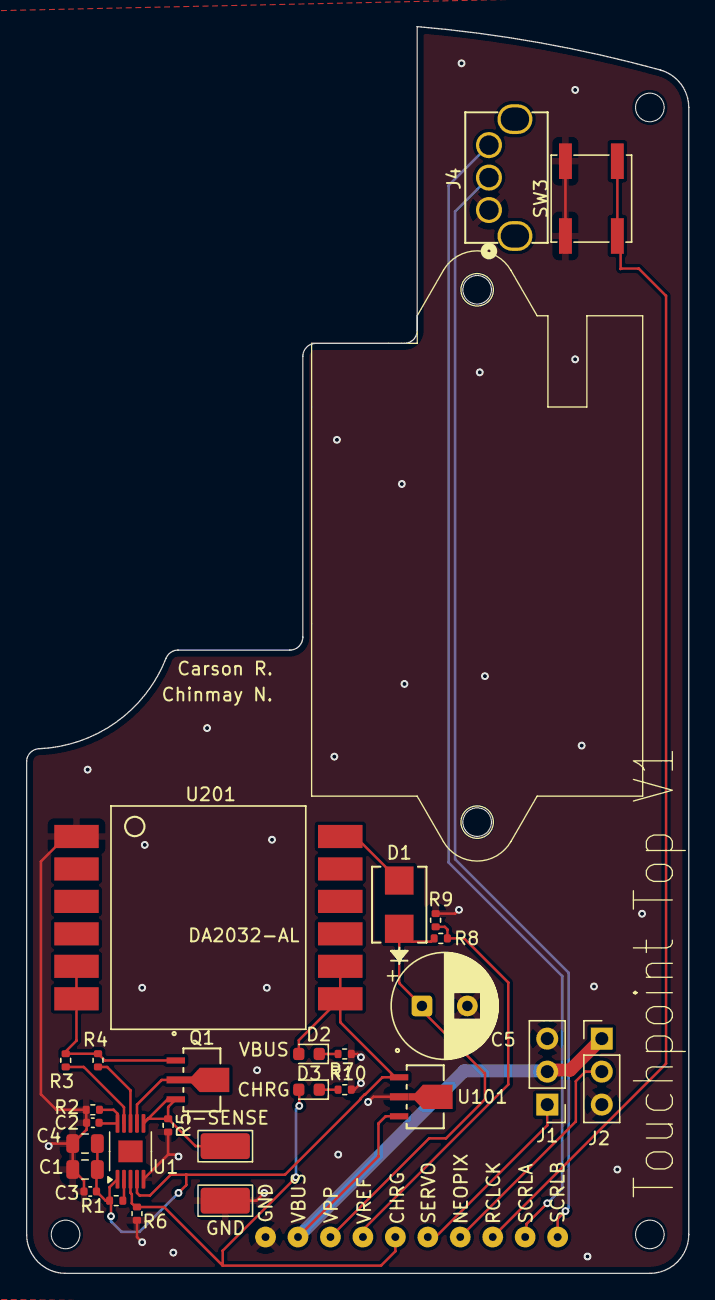
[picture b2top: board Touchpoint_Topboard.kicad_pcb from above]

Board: 2 copper layers, 51.0 x 96.0 mm, 29 parts (0 on the bottom side), 21 nets.

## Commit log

2026-02-09 Initial work on EEOP display PCB
2026-03-01 Finished EEOP PCB
2026-03-01 Updated board outline slightly
2026-03-01 Updated STEP file
2026-04-04 Added Flyback schematic documents
2026-04-04 Updated Relay with proper Driver and Transformer
2026-04-04 Finished wiring the right side of the transformer
2026-04-05 Added board outlines
2026-04-06 Populated most of mainboard schematic except for EEOP shift register
2026-04-07 FInished populating mainboard schematic
2026-04-09 Renamed topboard
2026-04-09 Added remaining interface things to topboard schematic
2026-04-10 Finished assigning most footprints
2026-04-10 Changed some component values based on availability
2026-04-11 Finished assigning footprints and 3d models for both boards
2026-04-11 Actually finished assigning footprints in 3d models
2026-04-11 Added 5V regulator to flyback converter
2026-04-11 Added servo mount outline
2026-04-11 Changed to jumper connector between boards
2026-04-11 Added 3.3V to interface
2026-04-11 Finished Routing and Placement of Top Board
2026-04-11 Added Via Stitching and Changed VBUS Trace
2026-04-11 Added minor final changes to schematic
2026-04-11 Working through mainboard routing
2026-04-12 Finally finished routing EEOP driver
2026-04-12 Almost finished routing mainboard
2026-04-13 Passed DRC
2026-04-13 Finished silkscreening
2026-04-13 Finished adjusting mechanical components
2026-04-13 Final changes for manufacturing
2026-04-15 Final manufacturing adjustments
2026-04-27 Fixed EEOP via size
2026-05-01 Fixed silkscreen label mixups
